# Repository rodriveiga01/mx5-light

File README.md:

# NA-Wink

Prototype controller for MX-5 pop-up headlights: ESP32 firmware, hardware
design, and companion app.

- `firmware/` — controller, BLE protocol, and host model.
- `hardware/` — harness, pinout, KiCad design, and circuit notes.
- `simulator/` — motor-free behavioral simulation.

Prototype only. Vehicle pinout, wiring, and hardware behavior still need
bench and donor-car validation; see `hardware/kicad/README.md`.

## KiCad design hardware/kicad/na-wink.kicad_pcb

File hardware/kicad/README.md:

# KiCad design

Sources: `na-wink.kicad_sch` (schematic) and `na-wink.kicad_pcb` (layout
draft). This is a review draft, not fabrication-ready.

- ERC: 0 errors. DRC: 22 unconnected GND items because CLI checks do not fill zones.
- Library remapping is required. Relay footprints are placeholders and must be corrected.
- Connector fit, motor current, relay rating, and relay polarity remain unverified.
- Do not order a board until layout checks and bench validation HV1–HV4 pass.

Reports: `hardware/exports/erc.rpt` and `hardware/exports/drc.rpt`.

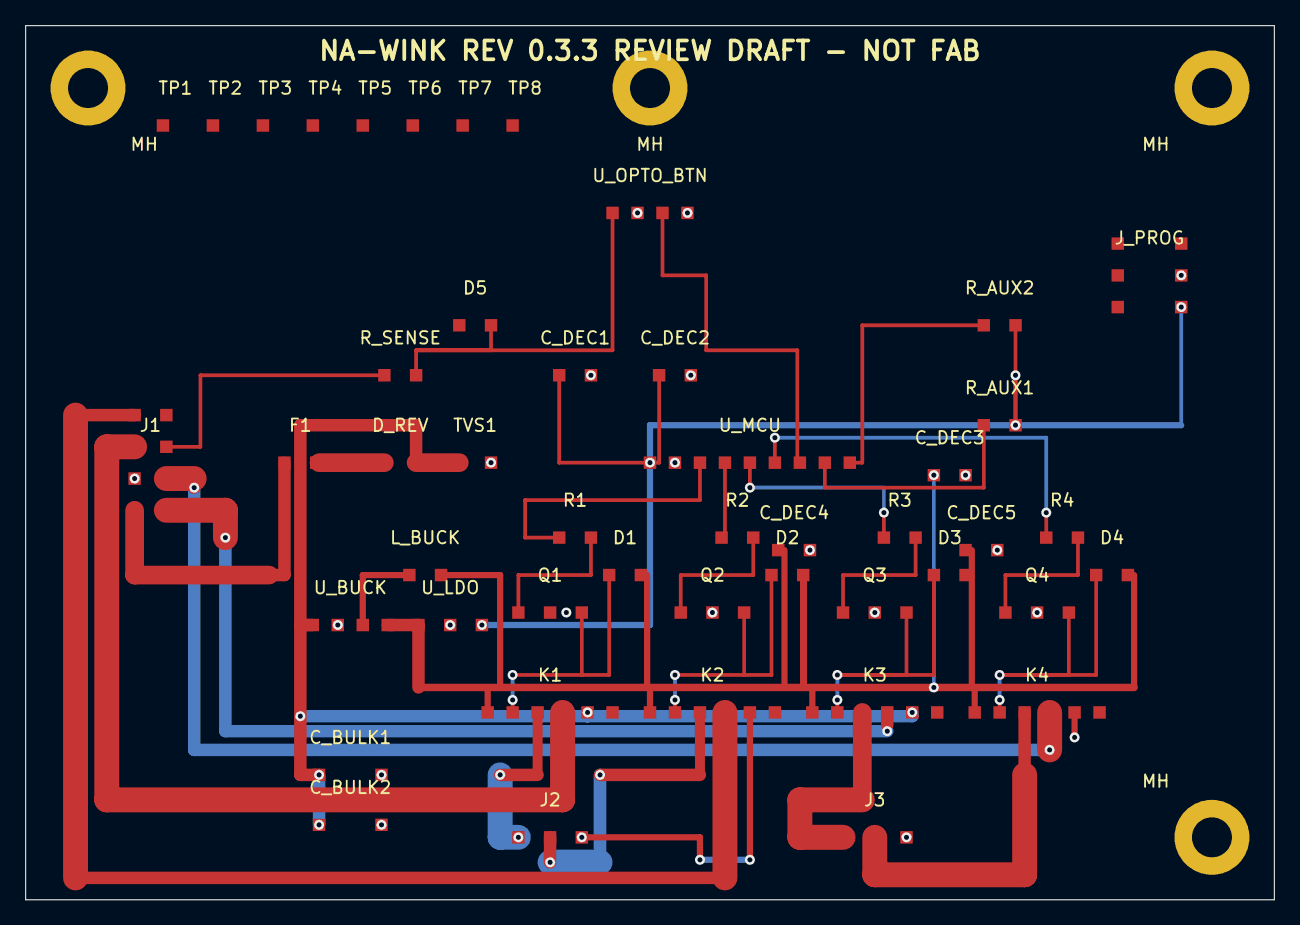
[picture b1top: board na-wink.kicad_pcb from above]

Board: 2 copper layers, 100.0 x 70.0 mm, 51 parts (0 on the bottom side), 32 nets.

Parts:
C_BULK1, C_BULK2: 470uF-50V; CP_Radial_D10
C_DEC1, C_DEC2, C_DEC3, C_DEC4, C_DEC5: 100nF-50V; C_0603
D1, D2, D3, D4: 1N4148-flyback; D_SOD-123
D5: 1N4148-revprot; D_SOD-123
D_REV: LM5050-ideal-diode-TBD; D_REV-LM5050-CSD18532-TBD
F1: 10A-ATO; ATO-blade
J1: MX120G-8
J2: MOTOR-L; MX120G-3
J3: MOTOR-R; MX120G-3
J_PROG: PROG; PinHeader_1x06
K1, K2, K3, K4: G2R-2-DC5; Omron_G2R-2
L_BUCK: 4U7; LX_4U7_TBD
MH: M3; MountingHole_3.2mm_M3
MH#2, MH#3, MH#4: M3; MountingHole_3.2mm_M3
Q1, Q2, Q3, Q4: MMBT2222A; SOT-23
R1, R2, R3, R4: 560R-0603; R_0603
R_AUX1, R_AUX2: 10k-0603; R_0603
R_SENSE: 590R-TBD-METERING; R_0603
TP1, TP2, TP3, TP4, TP5, TP6, TP7, TP8: TP; Loop_D2.5
TVS1: SMBJ26CA; Diodes_SMB
U_BUCK: LM46002; Buck-12V-5V
U_LDO: KF33BD; SOT-223
U_MCU: ESP32-S3; ESP32-S3-WROOM-1
U_OPTO_BTN: 4N25; DIP-6

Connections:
3V3: C_DEC1.1, C_DEC2.1, J_PROG.4, R_AUX1.2, R_AUX2.2, U_LDO.3, U_MCU.1
5V: C_DEC3.1, C_DEC4.1, C_DEC5.1, D1.2, D2.2, D3.2, D4.2, K1.1, K2.1, K3.1, K4.1, L_BUCK.2, U_BUCK.4, U_LDO.1
12V_PROTECTED: C_BULK1.1, C_BULK2.1, D_REV.2, K1.5, K3.5, TVS1.1, U_BUCK.1
AUX1: R_AUX1.1, U_MCU.8
AUX2: R_AUX2.1, U_MCU.9
BTN_SENSE: D5.2, R_SENSE.2, U_OPTO_BTN.1
GND: C_BULK1.2, C_BULK2.2, C_DEC1.2, C_DEC2.2, C_DEC3.2, C_DEC4.2, C_DEC5.2, D5.1, J1.2, J2.3, J3.3, J_PROG.5, K2.5, K4.5, Q1.2, Q2.2, Q3.2, Q4.2, TVS1.2, U_BUCK.2, U_LDO.2, U_MCU.2, U_OPTO_BTN.2, U_OPTO_BTN.4
MOTOR_L_A: J2.1, K1.3
MOTOR_L_B: J2.2, K2.3
MOTOR_R_A: J3.1, K3.3
MOTOR_R_B: J3.2, K4.3
N_G4R1: R1.1, U_MCU.3
N_G5R2: R2.1, U_MCU.4
N_G6R3: R3.1, U_MCU.5
N_G7R4: R4.1, U_MCU.6
N_J1_RSENSE: J1.7, R_SENSE.1
N_R1Q1: Q1.1, R1.2
N_R2Q2: Q2.1, R2.2
N_R3Q3: Q3.1, R3.2
N_R4Q4: Q4.1, R4.2
N_SENSE9: U_MCU.7, U_OPTO_BTN.3
N_SW: L_BUCK.1, U_BUCK.3
OEM_L_A: J1.3, K1.4
OEM_L_B: J1.4, K2.4
OEM_R_A: J1.5, K3.4
OEM_R_B: J1.6, K4.4
RELAY_L_COIL_A: D1.1, K1.2, Q1.3
RELAY_L_COIL_B: D2.1, K2.2, Q2.3
RELAY_R_COIL_A: D3.1, K3.2, Q3.3
RELAY_R_COIL_B: D4.1, K4.2, Q4.3
VBAT: F1.1, J1.1
VBAT_FUSED: D_REV.1, F1.2
